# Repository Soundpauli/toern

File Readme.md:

# TŒRN `[tɜːn]`

**Open-source sequencer and sampler** — by [warft_ctrl](mailto:info@toern.live)

> Say it like *turn*. As in: turn the knobs. Turn a doodle into a beat. Turn “I can’t play piano” into “wait, that slap though.”

TŒRN is a sequenced musical device for beginners, makers, and anyone who likes blinking lights more than plugin menus. Think **Etch-A-Sketch™ energy**, but instead of drawing a wobbly staircase you draw drums, synths, and happy accidents — on a vivid **32×16 RGB LED panel** (standard; 16×16 optional) that is both the screen *and* the keyboard.

It sits on a Teensy 4.1, runs from a Micro SD card full of your WAVs, and is happy on a desk, in a backpack, or on battery at the park where strangers will ask “what *is* that?”

**Status:** under very active development. Things move fast. Stay tuned, and don’t be surprised if yesterday’s weird bug is today’s charming feature (or the other way around).

---

## What it is (in plain language)

You get:

- **8 sample voices** for drums, one-shots, loops, and “that weird recording from the metro”
- **1 three-voice polyphonic synth** with presets (bass, keys, chiptune, pads… the usual suspects)
- **2 monophonic synths** with LFO and arpeggiator for leads that refuse to sit still
- A **32-step × 8-page** sequencer (256 steps of room to overthink; 16×16 mode uses 16 steps × 16 pages), page chaining into songs, MIDI in/out, filters, bitcrush, reverb, and enough real-time knobs to keep your hands busy and your laptop jealous

No laptop required once it’s built. Samples live on the SD card. Patterns autosave. You twist, tap, and suddenly it’s 2 a.m.

For the friendly guided tour (first beat in about a minute), open the **[handbook](docs/handbook/index.html)** in this repo.

---

## A tiny history

TŒRN builds on the legacy of the **NI404**, with more features, fewer cables dangling off the side, and a custom PCB where everything mounts cleanly. The older “extra boards and hope” era is over.

Meet the glow-up:

- **RGB-I2C rotary encoders** — smoother, prettier, and they light up like they mean it
- **Custom PCB** — codec, charging, and jacks on one board
- **USB-C** — because micro-USB was a character-building experience we no longer need
- **LiPo charging port** — optional battery for true “make beats on a train” energy (battery not included; we trust you with electricity)
- **Proper audio I/O** — 6.35 mm headphone out, line in/out, mic in, *plus* a built-in mic for “sample the room right now” moments
- **TRS MIDI in/out** — play nice with the rest of your setup
- **On/off switch** — underrated luxury
- **Touch buttons** — for the things knobs shouldn’t monopolize
- **Laser-cut acrylic case** — files included; looks finished, not “breadboard cosplay”
- **JST connectors** — expansion leads plug in

Open source as always: schematics, code, and design files are here for you to poke, fork, and improve.

---

## Feature list

### Sequencer

- **11 instrument voices** on a 16-row grid: 8 sample voices (1–8), one 3-voice poly synth (11), two mono synths (13–14)
- Standard **32 steps per page × 8 pages** → 256 steps per pattern; optional 16×16 mode uses 16 steps × 16 pages
- **Voice mode**: each voice keeps its own pattern length. It loops the pages that hold its notes, pitches included, while the other voices keep looping on their own
- **FIRE** (ETC → ADV menu): optional playhead sparks when a chosen voice’s notes light white
- Store up to **999 patterns**, **999 samples**, **999 samplepacks**
- **Autosave / autoload** so your 3 a.m. genius doesn’t vanish at boot
- **Switch patterns live** without stopping playback
- **Song mode**: chain up to **64** page assignments from the current pattern
- Pattern ops: copy/paste, transpose page/channel (±1 octave), smart random notes (major/minor + rhythm ideas), clear page/channel
- **SWAP** exchanges notes between voices, with octave offsets; optional **SUBP** file subpatterns extend arrangements

### Sample voices (channels 1–8)

- Up to **~12 seconds** per voice at 44.1 kHz
- Browse and load samples **while playing** (yes, really)
- Per-voice start/end trim, forward/reverse
- **TIME** stretches or shortens samples independently of pitch
- Samplepacks (including pack 0 = custom per-voice assignment)
- Record from **built-in mic / line-in / mic-in** straight in the sample browser
- Save or merge used samples back to the SD card as a pack

### Synth voices

**Channel 11 — poly synth**

- 3 oscillators per voice × 3 voices
- Presets: BASS, KEYS, CHPT, PAD, WOW, ORG, FLT, LEAD, ARP, BRSS
- Per-voice ADSR, filter envelope, pan, volume, pitch (cents & semitones), waveform

**Channels 13–14 — mono synths**

- 2 oscillators each
- ADSR, LFO on cutoff/resonance, MIDI arpeggiator (step/span; does not pitch-shift grid notes)
- Waveforms: sine, saw, square, triangle

### Effects (all channels)

- **ADSR** — attack / decay / sustain / release (0–32 range)
- **Bitcrusher** — bit depth 1–16 (0 = bypass), sample-rate reduction down to glorious crunch
- **Filter** — LP / HP / BP, 0–10 kHz, resonance 0.7–5.0, smooth transitions
- **Reverb** — room size, damping, wet/dry; denser six-comb/four-diffuser network on reverb-equipped voices
- Fast filter access on encoder #3 during runtime (assignable default per channel)

### MIDI, clock & extras

- TRS MIDI in/out, clock send/receive, notes, transport
- BPM **40–300**, internal clock, external MIDI clock, tap tempo via touch
- Live recording / looping (touch-hold), up to ~12 s per voice
- Note probability, velocity, condition triggers (those “only every other bar” tricks)
- Global transpose, per-channel detune & octave, fine cents on the poly synth
- Mute / solo, pattern modes (OFF, ON, SONG, NEXT)
- Stereo routing options
- USB **Audio + Serial**: send the mix to a computer while using the SD tool; musical MIDI uses the TRS ports
- Analog clock **out (J25)**, clock **in (J26)** and voice-triggered **sidechain out (J27)**
- **TOUCHY** performance pads, live fills, and per-voice audition
- Browser tools for firmware flashing, SD transfers, sample conversion and the simulator
- **Demo animation:** open **ETC → INFO**, press **touch3 / BUTTON_C**; press and release **Touch 1 / BUTTON_A** to return to INFO

---

## Tech specs

| | |
|---|---|
| **Brain** | Teensy 4.1, PSRAM fitted. Audio codec is the SGTL5000 on the carrier |
| **Memory** | 16 MB PSRAM target; Micro SD (handbook suggests up to 64 GB, SanDisk Ultra) |
| **Audio** | 44.1 kHz, 16-bit mono WAV |
| **Controls** | 4× RGB illuminated I2C rotary-push encoders, 5 capacitive touch buttons |
| **Display** | Standard [32×16 RGB LED panel](https://de.aliexpress.com/item/1005010071864259.html), 512 LEDs (FastLED); 16×16 optional |
| **I/O** | 6.35 mm headphones, line in/out, mic in; built-in mic; TRS MIDI in/out |
| **Power** | USB-C or optional LiPo + charging |

---

## Repo map (where stuff lives)

| Path | Contents |
|------|----------|
| `platformio/` | Arduino sketch tabs, headers, custom audio in `src/`, build scripts and `platformio.ini` |
| `hardware/PCB/` | KiCad boards, schematics, manufacturing files and [purchasing BOMs](hardware/PCB/BOM/README.md) |
| `hardware/housing/` | Fusion archives, laser DXFs and panel previews |
| `docs/devdocs/` | Developer documentation → [docs.toern.live](https://docs.toern.live/) |
| `docs/handbook/` | Operator handbook → [handbook.toern.live](https://handbook.toern.live/) |
| `docs/BUILD.md`, `docs/info.md` | Hardware assembly and firmware build instructions |
| `tools/firmware/` | Browser firmware flasher (GPL-3.0) |
| `tools/sdtool/` | Browser SD tool |
| `tools/sim/` | Browser simulator |
| `tools/audioconvert/` | Standalone sample converter |
| `tools/case/` | Standalone case generator; `case.toern.live` planned, not deployed |
| `tools/colorsheme/`, `tools/_shared/` | Color editor and shared tool assets |
| `_debug/` | Host tests, analysis scripts and local diagnostic captures |
| `_private/` | Local business data/helpers; annotation tool in `_private/helpers/annotate/` |
| `website/` | Public project website only; local/deploy-only |

See [the complete directory map](docs/REPOSITORY_LAYOUT.md) for local-only items marked `***`.

Build from the repository root with `pio run -d platformio`, or `cd platformio` first.

For a personal hardware build, follow the [assembly and laser-cutting guide](docs/BUILD.md).
Start with the [BOM directory](hardware/PCB/BOM/README.md): check assembly-part stock
before ordering the PCB. The [pre-order list](hardware/PCB/BOM/preorder-parts.csv)
lists parts to secure for JLCPCB assembly. Then buy the
Teensy, PSRAM, encoders, matrix, cables and
case hardware separately. The website’s **Build** chapter covers the same assembly order.

---

## External libraries & modifications

This project leans on several libraries. Some are stock; some got lovingly (and necessary-ly) poked.

### Modified

- **ResamplingReader.h** (`teensy-variable-playback`)
  Variable rates, interpolation, multi-channel, loop types (repeat / ping-pong), crossfading — in `platformio/src/resamplerReader.h`

- **Treeverb** (`effect_treeverb`)
  Full-rate reverb with balanced 6/4 diffusion in RAM1 — `platformio/src/effect_treeverb.*`; the older `effect_freeverb_dmabuf` remains a host-test reference.

- **FastLED**
  `FASTLED_ALLOW_INTERRUPTS 0` so LEDs and audio don’t argue mid-beat; custom `FastLEDshow()` / `FastLEDclear()` wrappers

- **MIDI**
  Bigger Serial8 buffers for dense clock traffic (`RX 2048`, `TX 128`) and custom TRS MIDI settings

### Standard / upstream

- **TeensyPolyphony** by Nic Newdigate — polyphonic heart of the thing
- **Audio Library** (PJRC)
- **WS2812Serial**, **i2cEncoderLibV2**, **FastTouch**

---

## Get one

Order a TŒRN at **[toern.live](https://toern.live/)**. Questions go to **info@toern.live**.

When it arrives, open the **[handbook](docs/handbook/index.html)** and start at First beat. Power is USB-C. A battery and a microSD card are not in the parcel; the buy page and the handbook hardware chapter name what to get.

Firmware changes: [`info.md`](docs/info.md) to flash, [`docs/devdocs/`](docs/devdocs) for how the code is shaped, [`firmware-edits`](docs/devdocs/docs/contributing/firmware-edits.md) for a new menu page. Fabricating a board from the design files is [`BUILD.md`](docs/BUILD.md) — that is not how a TŒRN is ordered.

---

## License

- **Software / code**: [MIT](LICENSE) — free for personal and commercial use.
- **Firmware loader** (`tools/firmware/`): [GPL-3.0](tools/firmware/LICENSE), because that tool is Teensy Loader Javascript. GPL-3.0 applies only to that folder.
- **Hardware design files** (schematics, PCB layouts, Gerbers, housings, etc.): [CC BY-NC 4.0](https://creativecommons.org/licenses/by-nc/4.0/) — personal / non-commercial use and modification. **Jan-Peter Kuntoff is the only person authorized to sell TŒRN hardware** (bare PCB, assembled PCB, kit, or unit), including boards sold **without a Teensy**. Teensy 4.1 is PJRC’s; it is not licensed in this repo. Anyone else needs written consent to sell.

Commercial hardware licensing: Jan aka **warft_ctrl** — info@toern.live (Hamburg, Germany)

---

## Thank you

Huge thanks to **Paul Stoffregen** and the PJRC crew for Teensy, to the wider open-source audio community, and an especially loud shoutout to **Nic Newdigate** for teensy-polyphony — basically the soul of this project.

Made with too many late nights and exactly the right number of RGB LEDs.

**Jan aka warft_ctrl** (formerly soundpauli)
Hamburg, 2026

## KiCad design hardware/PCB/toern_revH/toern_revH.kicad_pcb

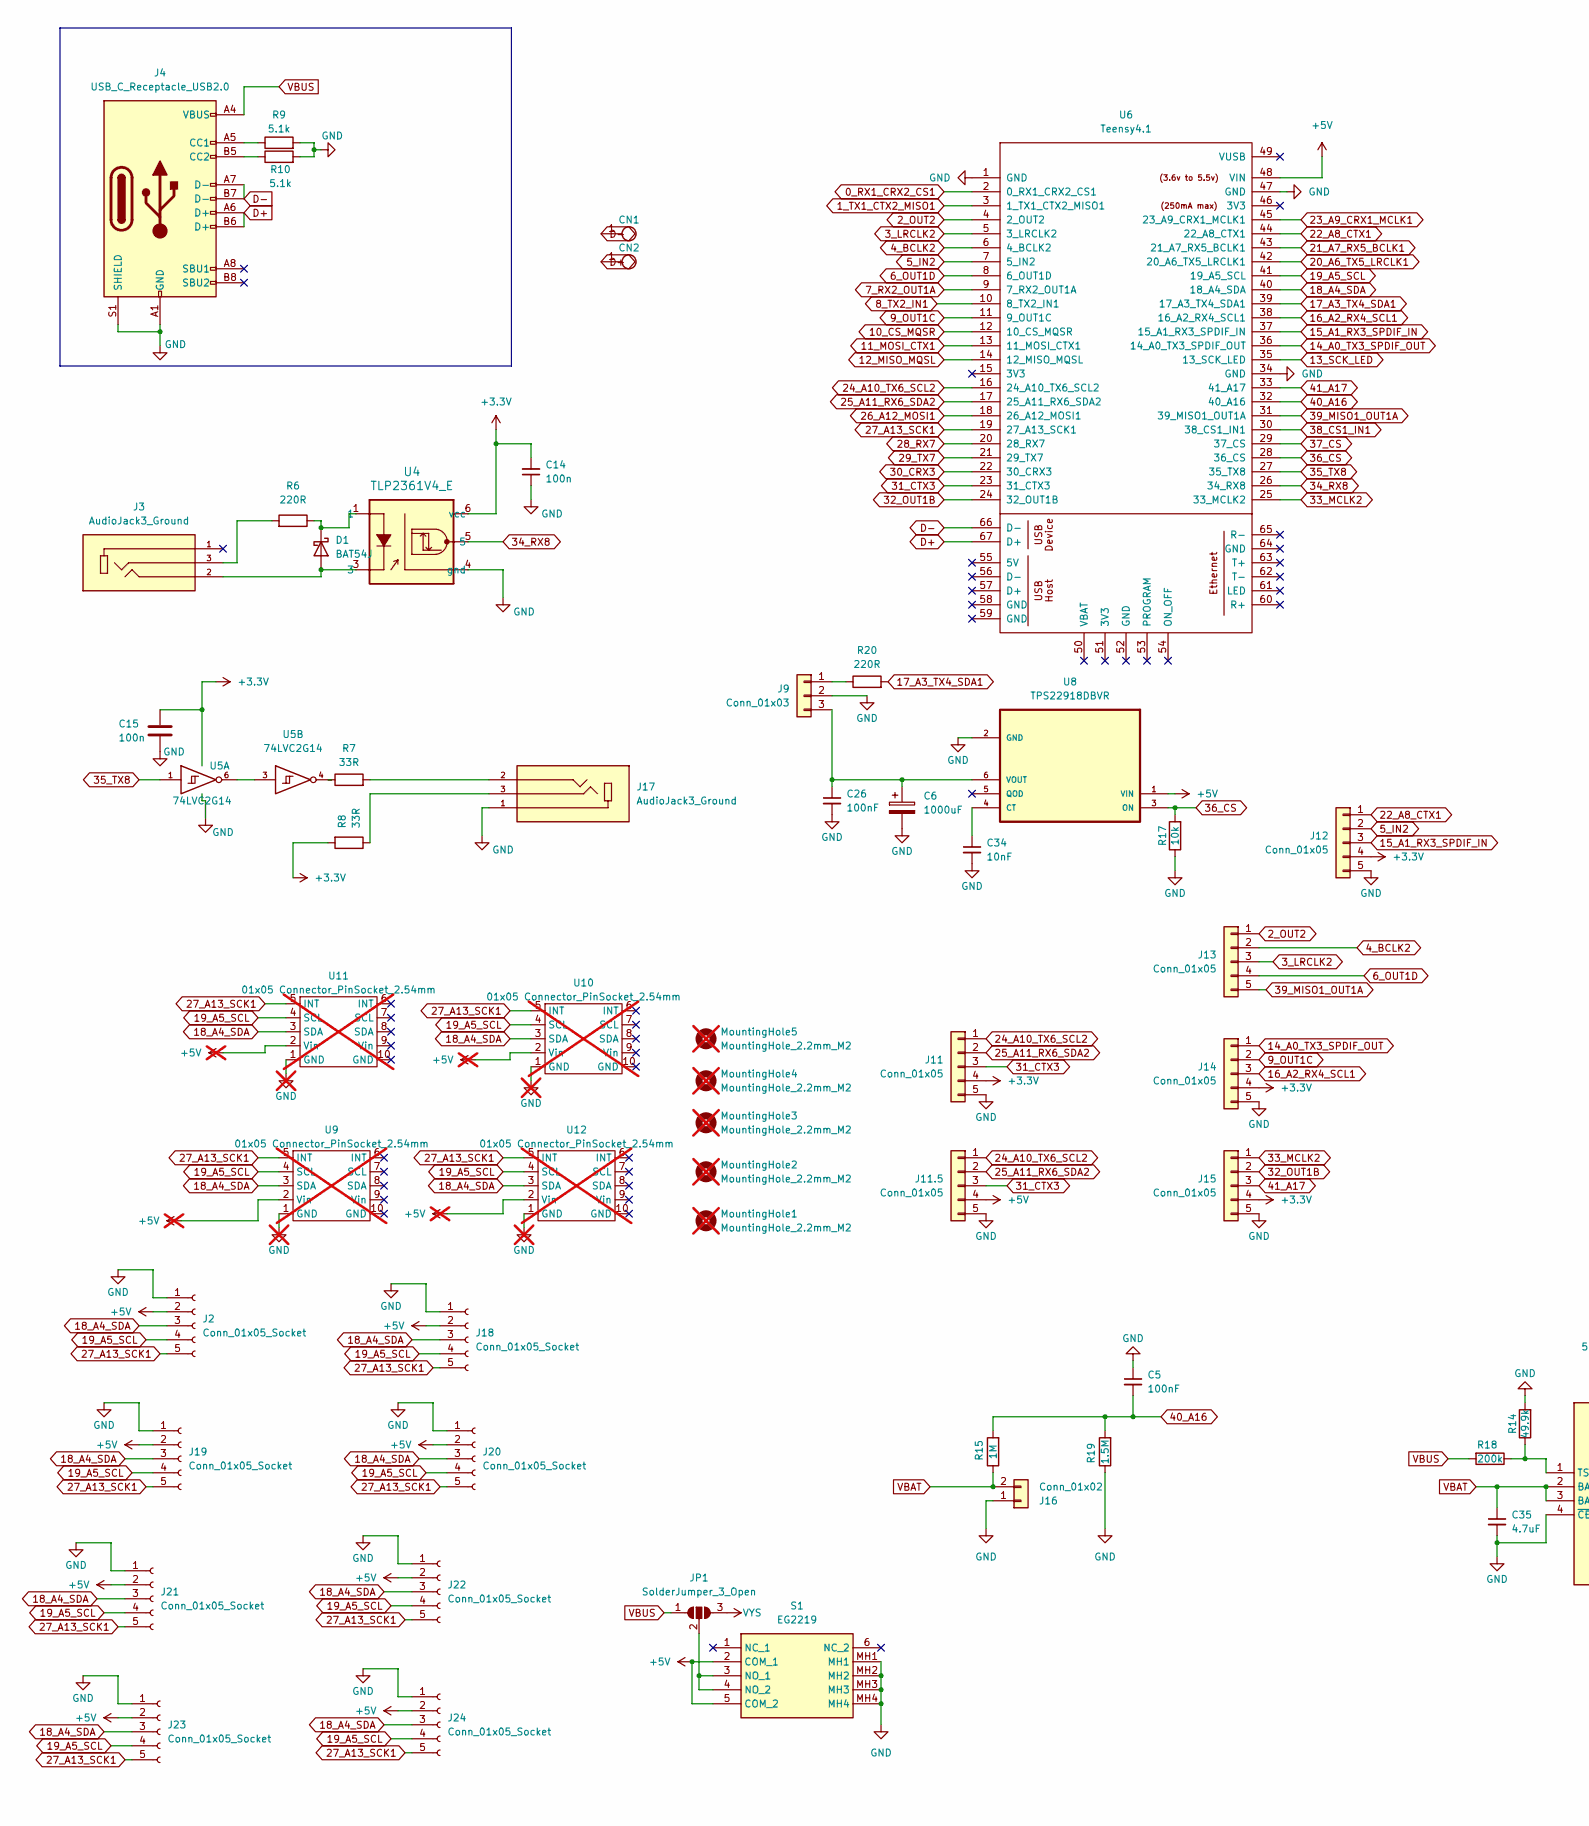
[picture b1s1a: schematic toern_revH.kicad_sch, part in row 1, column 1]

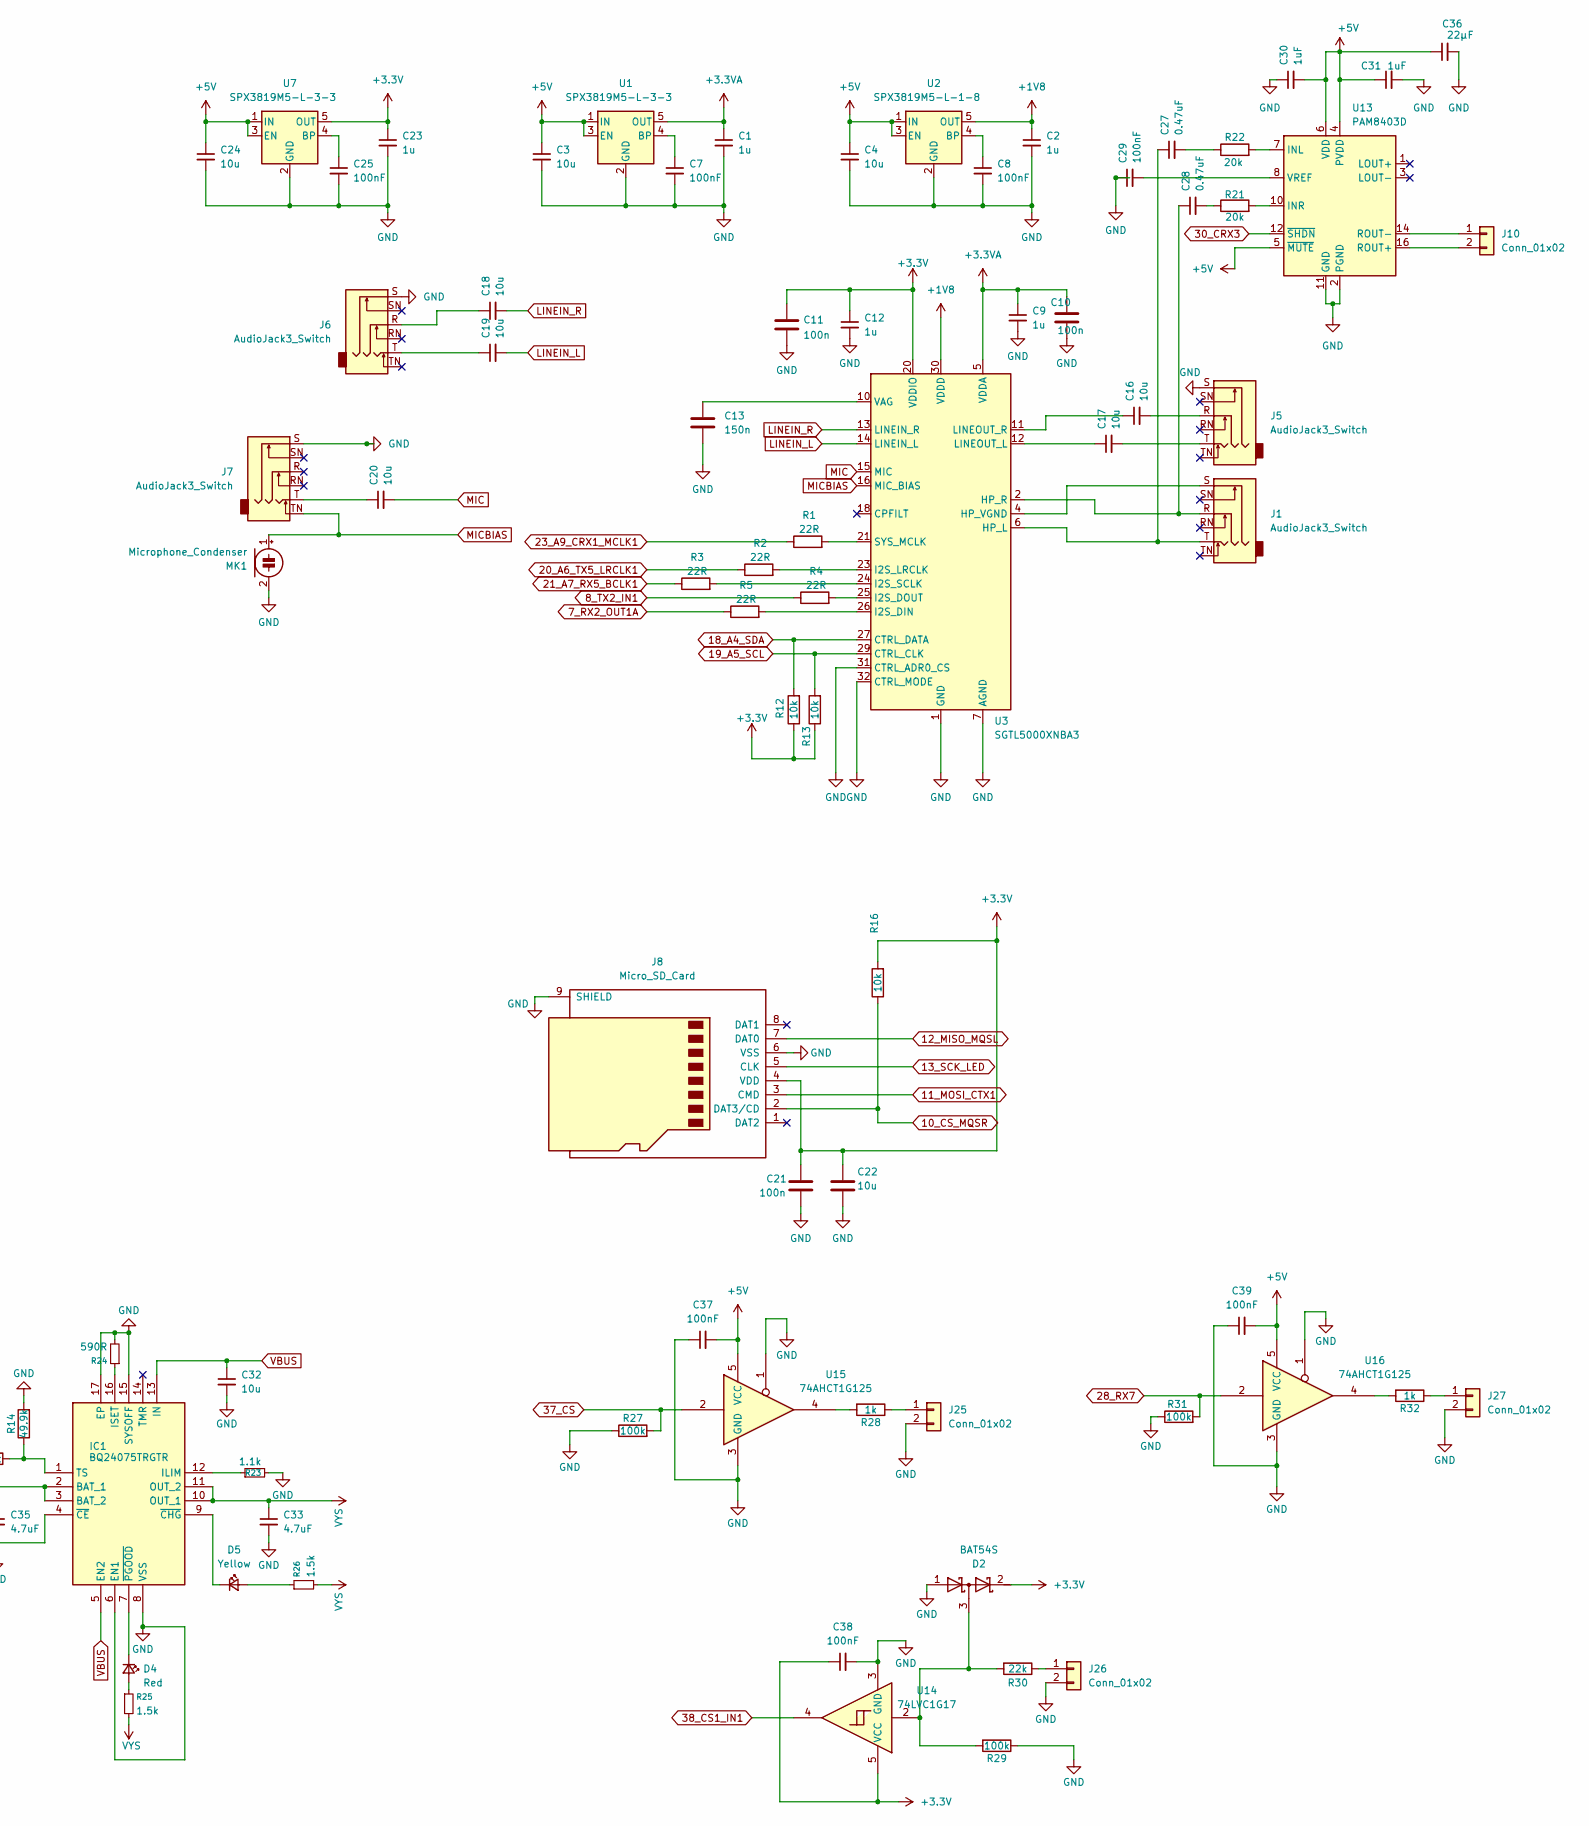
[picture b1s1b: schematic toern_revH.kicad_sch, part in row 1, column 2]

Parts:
C1, C2, C9, C12, C23: 1u; C_0402_1005Metric; lcsc# C52923
C3, C4, C16, C17, C18, C19, C20, C22, C24, C32: 10u; C_0603_1608Metric; lcsc# C19702
C5, C26, C29: 100nF; C_0603_1608Metric; lcsc# C1590
C6: 1000uF; CP_Elec_8x10.5; lcsc# C5686929
C7, C8, C25, C37, C38, C39: 100nF; C_0402_1005Metric; lcsc# C1525
C10, C11: 100n; C_0402_1005Metric; MPN CC0603KRX7R6BB224; lcsc# C77020
C13: 150n; C_0402_1005Metric; lcsc# C162182
C14, C15, C21: 100n; C_0402_1005Metric; lcsc# C77020
C27, C28: 0.47uF; C_0603_1608Metric; lcsc# C1623
C30, C31: 1uF; C_0603_1608Metric; lcsc# C15849
C33, C35: 4.7uF; C_0603_1608Metric; lcsc# C1705
C34: 10nF; C_0402_1005Metric; lcsc# C15195
C36: 22µF; C_0603_1608Metric; lcsc# C59461
CN1, CN2: YZP0354-20100-01; MPN YZP0354-20100-01; lcsc# C5157282
D1: BAT54J; D_SOD-323F; lcsc# C130415
D2: BAT54S; SOT-23; lcsc# C171786
D4: Red; LED_0402_1005Metric; lcsc# C71911
D5: Yellow; LED_0402_1005Metric; lcsc# C74342
IC1: BQ24075TRGTR; QFN50P300X300X100-17N-D; Mouser Part Number 595-BQ24075TRGTR
J1, J5, J6, J7: AudioJack3_Switch; Jack_6.35mm_Neutrik_NMJ6HCD2_Horizontal; lcsc# C368502
J2, J18, J19, J20, J21, J22, J23, J24: Conn_01x05_Socket; PinSocket_1x05_P2.54mm_Vertical; lcsc# C50950
J3, J17: AudioJack3_Ground; CUI_SJ1-3533; PARTREV 1.01; lcsc# C4991776
J4: USB_C_Receptacle_USB2.0; USB_C_Receptacle_HRO_TYPE-C-31-M-12; lcsc# C165948
J8: Micro_SD_Card; microSD_HC_Hirose_DM3BT-DSF-PEJS; lcsc# C597972
J9: Conn_01x03; JST_PH_B3B-PH-K_1x03_P2.00mm_Vertical; lcsc# C131339
J10, J16, J25, J26, J27: Conn_01x02; JST_PH_B2B-PH-K_1x02_P2.00mm_Vertical; lcsc# C131337
J11, J11.5, J12, J13, J14, J15: Conn_01x05; JST_PH_B5B-PH-K_1x05_P2.00mm_Vertical; lcsc# C157993
JP1: SolderJumper_3_Open; SolderJumper-3_P1.3mm_Open_RoundedPad1.0x1.5mm
MK1: Microphone_Condenser; MIC-TH_BD6.0-P1.90-D0.4-L-FD; lcsc# C529951
MountingHole1, MountingHole2, MountingHole3, MountingHole4, MountingHole5: MountingHole_2.2mm_M2; not fitted
R1, R2, R3, R4, R5: 22R; R_0402_1005Metric; lcsc# C25092
R6, R20: 220R; R_0603_1608Metric; lcsc# C22962
R7, R8: 33R; R_0603_1608Metric; lcsc# C23140
R9, R10: 5.1k; R_0402_1005Metric; lcsc# C25905
R12, R13, R16, R17: 10k; R_0402_1005Metric; lcsc# C25744
R14: 49.9k; R_0402_1005Metric; lcsc# C100457
R15: 1M; R_0402_1005Metric; lcsc# C26083
R18: 200k; R_0402_1005Metric; lcsc# C25764
R19: 1.5M; R_0402_1005Metric; lcsc# C11812
R21, R22: 20k; R_0805_2012Metric; LCSC C4328
R23: 1.1k; R_0402_1005Metric; lcsc# C25860
R24: 590R; R_0402_1005Metric; lcsc# C166635
R25, R26: 1.5k; R_0402_1005Metric; lcsc# C25867
R27, R29, R31: 100k; R_0402_1005Metric; lcsc# C25741
R28, R32: 1k; R_0402_1005Metric; lcsc# C11702
R30: 22k; R_0402_1005Metric; lcsc# C25768
S1: EG2219; Mouser Part Number 612-EG2219
U1, U7: SPX3819M5-L-3-3; SOT-23-5; lcsc# C9055
U2: SPX3819M5-L-1-8; SOT-23-5; lcsc# C24639
U3: SGTL5000XNBA3; QFN-32-1EP_5x5mm_P0.5mm_EP3.6x3.6mm; lcsc# C5196742
U4: TLP2361V4_E; 5pin SO6_TOS; lcsc# C107626
U5: 74LVC2G14; SOT-23-6; LCSC Part # C12401
U6: Teensy4.1; Teensy41; lcsc# ----
U8: TPS22918DBVR; SOT95P280X145-6N; lcsc# C131941
U9, U10, U11, U12: 01x05 Connector_PinSocket_2.54mm; DuppaI2CEncoderV2.1; lcsc# C50950; not fitted
U13: PAM8403D; SOIC-16_3.9x9.9mm_P1.27mm; lcsc# C17337
U14: 74LVC1G17; SOT-23-5; lcsc# C7836
U15, U16: 74AHCT1G125; SOT-23-5; lcsc# C7484

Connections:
0_RX1_CRX2_CS1: U6.2 (0_RX1_CRX2_CS1)
1_TX1_CTX2_MISO1: U6.3 (1_TX1_CTX2_MISO1)
2_OUT2: J13.1, U6.4 (2_OUT2); also elsewhere on the board
3_LRCLK2: J13.3, U6.5 (3_LRCLK2); also elsewhere on the board
4_BCLK2: J13.2, U6.6 (4_BCLK2); also elsewhere on the board
5_IN2: J12.2, U6.7 (5_IN2); also elsewhere on the board
6_OUT1D: J13.4, U6.8 (6_OUT1D); also elsewhere on the board
7_RX2_OUT1A: R5.1, U6.9 (7_RX2_OUT1A)
8_TX2_IN1: R4.1, U6.10 (8_TX2_IN1)
9_OUT1C: J14.2, U6.11 (9_OUT1C); also elsewhere on the board
10_CS_MQSR: J8.2 (DAT3/CD), R16.1, U6.12 (10_CS_MQSR)
11_MOSI_CTX1: J8.3 (CMD), U6.13 (11_MOSI_CTX1)
12_MISO_MQSL: J8.7 (DAT0), U6.14 (12_MISO_MQSL)
13_SCK_LED: J8.5 (CLK), U6.35 (13_SCK_LED)
14_A0_TX3_SPDIF_OUT: J14.1, U6.36 (14_A0_TX3_SPDIF_OUT); also elsewhere on the board
15_A1_RX3_SPDIF_IN: J12.3, U6.37 (15_A1_RX3_SPDIF_IN); also elsewhere on the board
16_A2_RX4_SCL1: J14.3, U6.38 (16_A2_RX4_SCL1); also elsewhere on the board
17_A3_TX4_SDA1: R20.2, U6.39 (17_A3_TX4_SDA1)
18_A4_SDA: J2.3, J18.3, J19.3, J20.3, J21.3, J22.3, J23.3, J24.3, R12.2, U3.27 (CTRL_DATA), U6.40 (18_A4_SDA), U9.3 (SDA), U10.3 (SDA), U11.3 (SDA), U12.3 (SDA)
19_A5_SCL: J2.4, J18.4, J19.4, J20.4, J21.4, J22.4, J23.4, J24.4, R13.2, U3.29 (CTRL_CLK), U6.41 (19_A5_SCL), U9.4 (SCL), U10.4 (SCL), U11.4 (SCL), U12.4 (SCL)
20_A6_TX5_LRCLK1: R2.1, U6.42 (20_A6_TX5_LRCLK1)
21_A7_RX5_BCLK1: R3.1, U6.43 (21_A7_RX5_BCLK1)
22_A8_CTX1: J12.1, U6.44 (22_A8_CTX1); also elsewhere on the board
23_A9_CRX1_MCLK1: R1.1, U6.45 (23_A9_CRX1_MCLK1)
24_A10_TX6_SCL2: J11.1, J11.5.1, U6.16 (24_A10_TX6_SCL2); also elsewhere on the board
25_A11_RX6_SDA2: J11.2, J11.5.2, U6.17 (25_A11_RX6_SDA2); also elsewhere on the board
26_A12_MOSI1: U6.18 (26_A12_MOSI1)
27_A13_SCK1: J2.5, J18.5, J19.5, J20.5, J21.5, J22.5, J23.5, J24.5, U6.19 (27_A13_SCK1), U9.5 (INT), U10.5 (INT), U11.5 (INT), U12.5 (INT)
28_RX7: R31.2, U6.20 (28_RX7), U16.2
29_TX7: U6.21 (29_TX7)
30_CRX3: U6.22 (30_CRX3), U13.12 (~SHDN)
31_CTX3: J11.3, J11.5.3, U6.23 (31_CTX3); also elsewhere on the board
32_OUT1B: J15.2, U6.24 (32_OUT1B)
33_MCLK2: J15.1, U6.25 (33_MCLK2)
34_RX8: U4.5, U6.26 (34_RX8)
35_TX8: U5.1, U6.27 (35_TX8)
36_CS: R17.2, U6.28 (36_CS), U8.3 (ON)
37_CS: R27.2, U6.29 (37_CS), U15.2
38_CS1_IN1: U6.30 (38_CS1_IN1), U14.4
39_MISO1_OUT1A: J13.5, U6.31 (39_MISO1_OUT1A); also elsewhere on the board
40_A16: C5.2, R15.2, R19.2, U6.32 (40_A16)
41_A17: J15.3, U6.33 (41_A17)
+1V8: C2.1, U2.5 (OUT), U3.30 (VDDD)
+3.3V: C11.1, C12.1, C14.2, C15.1, C21.2, C22.1, C23.1, C38.1, D2.2 (K), J8.4 (VDD), J11.4, J12.4, J14.4, J15.4, R8.2, R12.1, R13.1, R16.2, U3.20 (VDDIO), U4.6 (vcc), U5.5 (VCC), U7.5 (OUT), U14.5 (VCC); also elsewhere on the board
+3.3VA: C1.1, C9.1, C10.1, U1.5 (OUT), U3.5 (VDDA)
+5V: C3.1, C4.1, C24.1, C30.2, C31.1, C36.1, C37.2, C39.2, J2.2, J11.5.4, J18.2, J19.2, J20.2, J21.2, J22.2, J23.2, J24.2, S1.2 (COM_1), S1.5 (COM_2), U1.1 (IN), U1.3 (EN), U2.1 (IN), U2.3 (EN), U6.48 (VIN), U7.1 (IN), U7.3 (EN), U8.1 (VIN), U9.2 (Vin), U10.2 (Vin), U11.2 (Vin), U12.2 (Vin), U13.4 (PVDD), U13.5 (~MUTE), U13.6 (VDD), U13.13 (PVDD), U15.5 (VCC), U16.5 (VCC); also elsewhere on the board
D+: CN2.1 (CONTACT), J4.A6 (D+), J4.B6 (D+), U6.67 (D+)
D-: CN1.1 (CONTACT), J4.A7 (D-), J4.B7 (D-), U6.66 (D-)
GND: C1.2, C2.2, C3.2, C4.2, C5.1, C6.2, C7.2, C8.2, C9.2, C10.2, C11.2, C12.2, C13.2, C14.1, C15.2, C21.1, C22.2, C23.2, C24.2, C25.2, C26.2, C29.1, C30.1, C31.2, C32.2, C33.2, C34.2, C35.2, C36.2, C37.1, C38.2, C39.1, D2.1 (A), IC1.4 (~CE), IC1.6 (EN1), IC1.8 (VSS), IC1.15 (SYSOFF), IC1.17 (EP), J2.1, J4.A1 (GND), J4.A12 (GND), J4.B1 (GND), J4.B12 (GND), J4.S1 (SHIELD), J5.S, J6.S, J7.S, J8.6 (VSS), J8.9 (SHIELD), J9.2, J11.5, J11.5.5, J12.5, J14.5, J15.5, J16.1, J17.1, J18.1, J19.1, J20.1, J21.1, J22.1, J23.1, J24.1, J25.2, J26.2, J27.2, MK1.2 (-), R9.2, R10.2, R14.2, R17.1, R19.1, R23.2, R24.2, R27.1, R29.1, R31.1, S1.MH1, S1.MH2, S1.MH3, S1.MH4, U1.2 (GND), U2.2 (GND), U3.1 (GND), U3.3 (GND), U3.7 (AGND), U3.31 (CTRL_ADR0_CS), U3.32 (CTRL_MODE), U3.33 (GND), U4.4 (gnd), U5.2 (GND), U6.1 (GND), U6.34 (GND), U6.47 (GND), U7.2 (GND), U8.2 (GND), U9.1 (GND), U10.1 (GND), U11.1 (GND), U12.1 (GND), U13.2 (PGND), U13.11 (GND), U13.15 (PGND), U14.3 (GND), U15.1, U15.3 (GND), U16.1, U16.3 (GND); also elsewhere on the board
LINEIN_L: C19.2, U3.14 (LINEIN_L)
LINEIN_R: C18.2, U3.13 (LINEIN_R)
MIC: C20.2, U3.15 (MIC)
MICBIAS: J7.TN, MK1.1 (+), U3.16 (MIC_BIAS)
unnamed: C16.2, J5.R
unnamed: C17.2, J5.T
unnamed: C18.1, J6.R
unnamed: C19.1, J6.T
unnamed: C20.1, J7.T
unnamed: C27.2, R22.1
unnamed: C28.2, R21.1
unnamed: D1.2 (A), J3.2, U4.3
unnamed: D1.1 (K), R6.1, U4.1
unnamed: D2.3 (common), R29.2, R30.2, U14.2
unnamed: D4.2 (A), R25.1
unnamed: D4.1 (K), IC1.7 (~PGOOD)
unnamed: D5.2 (A), R26.1
unnamed: D5.1 (K), IC1.9 (~CHG)
unnamed: IC1.12 (ILIM), R23.1
unnamed: IC1.16 (ISET), R24.1
unnamed: IC1.1 (TS), R14.1, R18.1
unnamed: J3.3, R6.2
unnamed: J4.A5 (CC1), R9.1
unnamed: J4.B5 (CC2), R10.1
unnamed: J9.1, R20.1
unnamed: C6.1, C26.1, J9.3, U8.6 (VOUT)
unnamed: J10.1, U13.14 (ROUT-)
unnamed: J10.2, U13.16 (ROUT+)
unnamed: J17.2, R7.2
unnamed: J17.3, R8.1
unnamed: J25.1, R28.1
unnamed: J26.1, R30.1
unnamed: J27.1, R32.1
unnamed: JP1.2 (C), S1.3 (NO_1), S1.4 (NO_2)
unnamed: R7.1, U5.4
unnamed: R28.2, U15.4
unnamed: R32.2, U16.4
unnamed: C7.1, U1.4 (BP)
unnamed: C8.1, U2.4 (BP)
unnamed: C27.1, J1.T, U3.6 (HP_L)
unnamed: C28.1, J1.R, U3.2 (HP_R)
unnamed: J1.S, U3.4 (HP_VGND)
unnamed: R5.2, U3.26 (I2S_DIN)
unnamed: R4.2, U3.25 (I2S_DOUT)
unnamed: R2.2, U3.23 (I2S_LRCLK)
unnamed: R3.2, U3.24 (I2S_SCLK)
unnamed: C17.1, U3.12 (LINEOUT_L)
unnamed: C16.1, U3.11 (LINEOUT_R)
unnamed: R1.2, U3.21 (SYS_MCLK)
unnamed: C13.1, U3.10 (VAG)
unnamed: U5.3, U5.6
unnamed: C25.1, U7.4 (BP)
unnamed: C34.1, U8.4 (CT)
unnamed: R22.2, U13.7 (INL)
unnamed: R21.2, U13.10 (INR)
unnamed: C29.2, U13.8 (VREF)
VBAT: C35.1, IC1.2 (BAT_1), IC1.3 (BAT_2), J16.2, R15.1
VBUS: C32.1, IC1.5 (EN2), IC1.13 (IN), J4.A4 (VBUS), J4.A9 (VBUS), J4.B4 (VBUS), J4.B9 (VBUS), JP1.1 (A), R18.2
VYS: C33.1, IC1.10 (OUT_1), IC1.11 (OUT_2), JP1.3 (B), R25.2, R26.2

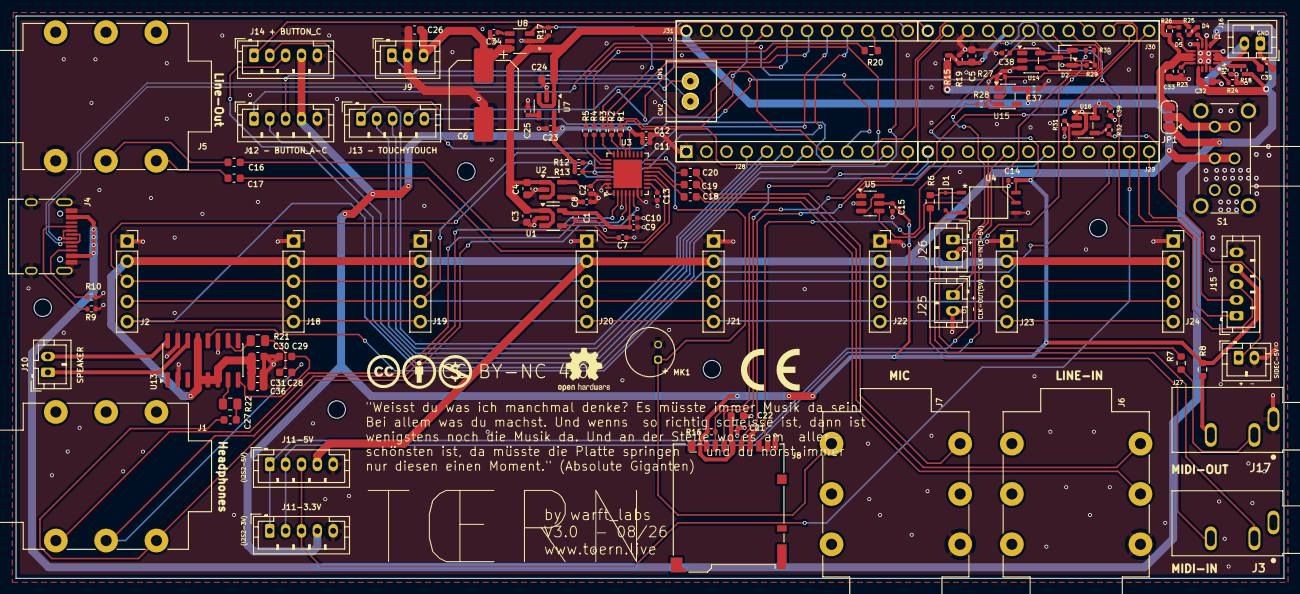
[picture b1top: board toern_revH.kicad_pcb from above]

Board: 4 copper layers, 160.0 x 71.0 mm, 130 parts (0 on the bottom side), 104 nets.

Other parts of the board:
J11-3.3V, J11-5V, J12 - BUTTON_A-C, J13 - TOUCHYTOUCH, J14 + BUTTON_C: Conn_01x05; JST_PH_B5B-PH-K_1x05_P2.00mm_Vertical
J28, J29, J30, J31: 929870-01-12-RA; 3M_929870-01-12-RA_Assembly
LOGOOPENHARDWARE: OSHW-Logo2_7.3x6mm_SilkScreen

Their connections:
2_OUT2: J13 - TOUCHYTOUCH.1; also elsewhere on the board
3_LRCLK2: J13 - TOUCHYTOUCH.3; also elsewhere on the board
4_BCLK2: J13 - TOUCHYTOUCH.2; also elsewhere on the board
5_IN2: J12 - BUTTON_A-C.2; also elsewhere on the board
6_OUT1D: J13 - TOUCHYTOUCH.4; also elsewhere on the board
9_OUT1C: J14 + BUTTON_C.2; also elsewhere on the board
14_A0_TX3_SPDIF_OUT: J14 + BUTTON_C.1; also elsewhere on the board
15_A1_RX3_SPDIF_IN: J12 - BUTTON_A-C.3; also elsewhere on the board
16_A2_RX4_SCL1: J14 + BUTTON_C.3; also elsewhere on the board
22_A8_CTX1: J12 - BUTTON_A-C.1; also elsewhere on the board
24_A10_TX6_SCL2: J11-3.3V.1, J11-5V.1; also elsewhere on the board
25_A11_RX6_SDA2: J11-3.3V.2, J11-5V.2; also elsewhere on the board
31_CTX3: J11-3.3V.3, J11-5V.3; also elsewhere on the board
39_MISO1_OUT1A: J13 - TOUCHYTOUCH.5; also elsewhere on the board
+3.3V: J11-3.3V.4, J12 - BUTTON_A-C.4, J14 + BUTTON_C.4; also elsewhere on the board
+5V: J11-5V.4; also elsewhere on the board
GND: J11-3.3V.5, J11-5V.5, J12 - BUTTON_A-C.5, J14 + BUTTON_C.5; also elsewhere on the board

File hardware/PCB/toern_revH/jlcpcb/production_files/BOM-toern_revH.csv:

Comment,Designator,Footprint,LCSC,Quantity
0.47uF,"C27,C28",C_0603_1608Metric,C1623,2
1.1k,R23,R_0402_1005Metric,C25860,1
1.5M,R19,R_0402_1005Metric,C11812,1
1.5k,"R25,R26",R_0402_1005Metric,C25867,2
1000uF,C6,CP_Elec_8x10.5,C5686929,1
100k,"R27,R29,R31",R_0402_1005Metric,C25741,3
100n,"C10,C11,C14,C15,C21",C_0402_1005Metric,C77020,5
100nF,"C25,C37,C38,C39,C7,C8",C_0402_1005Metric,C1525,6
100nF,"C26,C29,C5",C_0603_1608Metric,C1590,3
10k,"R12,R13,R16,R17",R_0402_1005Metric,C25744,4
10nF,C34,C_0402_1005Metric,C15195,1
10u,"C16,C17,C18,C19,C20,C22,C24,C3,C32,C4",C_0603_1608Metric,C19702,10
150n,C13,C_0402_1005Metric,C162182,1
1M,R15,R_0402_1005Metric,C26083,1
1k,"R28,R32",R_0402_1005Metric,C11702,2
1u,"C1,C12,C2,C23,C9",C_0402_1005Metric,C52923,5
1uF,"C30,C31",C_0603_1608Metric,C15849,2
200k,R18,R_0402_1005Metric,C25764,1
20k,"R21,R22",R_0805_2012Metric,C4328,2
220R,"R20,R6",R_0603_1608Metric,C22962,2
22R,"R1,R2,R3,R4,R5",R_0402_1005Metric,C25092,5
22k,R30,R_0402_1005Metric,C25768,1
22µF,C36,C_0603_1608Metric,C59461,1
33R,"R7,R8",R_0603_1608Metric,C23140,2
4.7uF,"C33,C35",C_0603_1608Metric,C1705,2
49.9k,R14,R_0402_1005Metric,C100457,1
5.1k,"R10,R9",R_0402_1005Metric,C25905,2
590R,R24,R_0402_1005Metric,C166635,1
74AHCT1G125,"U15,U16",SOT-23-5,C7484,2
74LVC1G17,U14,SOT-23-5,C7836,1
74LVC2G14,U5,SOT-23-6,C12401,1
AudioJack3_Ground,"J17,J3",CUI_SJ1-3533,C4991776,2
AudioJack3_Switch,"J1,J5,J6,J7",Jack_6.35mm_Neutrik_NMJ6HCD2_Horizontal,C368502,4
BAT54J,D1,D_SOD-323F,C130415,1
BAT54S,D2,SOT-23,C171786,1
BQ24075TRGTR,IC1,QFN50P300X300X100-17N-D,C544783,1
Conn_01x02,"J10,J16,J25,J26,J27",JST_PH_B2B-PH-K_1x02_P2.00mm_Vertical,C131337,5
Conn_01x03,J9,JST_PH_B3B-PH-K_1x03_P2.00mm_Vertical,C131339,1
Conn_01x05,"J32,J11,J12,J13,J14,J15",JST_PH_B5B-PH-K_1x05_P2.00mm_Vertical,C157993,6
Conn_01x05_Socket,"J18,J19,J2,J20,J21,J22,J23,J24",PinSocket_1x05_P2.54mm_Vertical,C50950,8
EG2219,S1,EG2219,C3664594,1
Micro_SD_Card,J8,microSD_HC_Hirose_DM3BT-DSF-PEJS,C597972,1
Microphone_Condenser,MK1,MIC-TH_BD6.0-P1.90-D0.4-L-FD,C529951,1
PAM8403D,U13,SOIC-16_3.9x9.9mm_P1.27mm,C17337,1
Red,D4,LED_0402_1005Metric,C71911,1
SGTL5000XNBA3,U3,QFN-32-1EP_5x5mm_P0.5mm_EP3.6x3.6mm,C5196742,1
SPX3819M5-L-1-8,U2,SOT-23-5,C24639,1
SPX3819M5-L-3-3,"U1,U7",SOT-23-5,C9055,2
TLP2361V4_E,U4,5pin SO6_TOS,C107626,1
TPS22918DBVR,U8,SOT95P280X145-6N,C131941,1
USB_C_Receptacle_USB2.0,J4,USB_C_Receptacle_HRO_TYPE-C-31-M-12,C165948,1
YZP0354-20100-01,"CN1,CN2",YZP0354-20100-01,C5157282,2
Yellow,D5,LED_0402_1005Metric,C74342,1

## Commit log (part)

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2025-01-27 added MIDI-IN
2025-02-03 starting adsr implementation + bugfixing
2025-02-04 bugfixes for playback and filebrowser
2025-02-07 cleaning up files
2025-02-13 fixed bug with posString
2025-02-17 fixed sample-splicing
2025-02-26 added UI for filters
2025-02-28 splitted main files to clean
2025-03-19 added filters for V13
2025-03-19 completed synth integration 11-14
2025-03-24 added drums for ch1-3
2025-03-25 fixed filters and bugfixes plus menu
2025-03-28 Update LICENSE
    Changed HW license to CC by nc
2025-03-28 fixed sample loading and editing
2025-03-29 fixed midi In Clock
2025-03-29 fixed midi in and out
2025-03-30 fixed midi
2025-04-04 added multi osc and drums for ch1-4
2025-04-06 fixed memory issues
2025-04-08 fixed ram problems
2025-04-11 further fixed for filters and voices
2025-04-16 more fixes for synths and freqs
2025-04-24 more bugfixes and features
2025-04-26 fixed sample cutting
2025-04-29 fixed sampler and midi + ui
2025-05-07 additional bugfixes
2025-05-11 bugfixes and delay timings
2025-05-20 added touch and realtime recording
2025-05-23 fixed BPM calculations for midi
2025-05-23 fixed midi transport
2025-05-24 fixed settings and menu
2025-05-26 added fast-recording via 3.5mm pedal
2025-06-17 fixed playback and midi
2025-06-17 fixed wav selection
2025-06-18 added PMOD patternmode
2025-07-07 flattend audio setup, fixed bugs with memory during play
2025-07-15 new filter views
2025-08-21 bugfixes
2025-09-11 further bugfixes
2025-09-13 added AI
2025-09-18 bugfixes and added filters
2025-09-19 bugfixes for encoderlights and midi
2025-09-26 added subpattern mode
2025-10-04 more bugfixes and some features
2025-10-18 fixing samplepack saving
2025-10-18 fixing sampl search and midi mode
2025-10-18 added reverse samples
2025-10-18 added bugfixes for ai
2025-10-21 cleanup and new menu, songmode
2025-10-21 cleanup and new menu, songmode2
2025-10-22 added probabilies
2025-10-22 added probabilies fix
2025-10-22 added fix for multiple panels
2025-10-23 adding fixes for eepromcrash
2025-10-25 fixed reset and memory
2025-10-28 back to working version after memory/pong fail
2025-11-07 fixed recording
2025-11-08 memory opt and bugfixes
2025-11-08 memory opt and bugfixes2
2025-11-09 added PONG
2025-11-09 PONG fixes
2025-11-11 added CTRL mode play/vol
2025-11-15 fixed midi sync
2025-11-15 fixed midi sync and transport
2025-11-19 matze hat geregelt - midi läuft
2025-11-20 looper recording fixed
2025-11-25 fixed midi finally
2025-11-25 fixed midi finally + autosave fix
2025-11-26 added condition triggers
2025-11-26 added condition triggers - advanced
2025-11-26 fixed fastfilters
2025-11-26 fixed button debounce 30ms ghostplaypause
2025-11-27 fixed button debounce 30ms ghostplaypause 2
2025-11-27 changes in monitoring-in
2025-11-27 changes in monitoring-in 2
2025-11-28 changes for bpm, rec and helpers
2025-11-30 fixed memory issues with large samples
2025-12-01 fixed overflows on long runs
2025-12-06 fixes for ram1, freeverbs and more
2025-12-06 fixes for ch11 fastfilter
2025-12-06 fixes for midi channels and loudness
2025-12-06 fixed synth voices, removed DRUMS
2025-12-06 added LFO and ARPEGGIATOR ch13+14
2025-12-14 performance fix and filenames
2025-12-14 syth filter and defaults deeper
2025-12-15 UX bugfixes
2025-12-15 auto generation for NEW
2025-12-18 added alternatie draw method
2025-12-22 further fixes for menu
2025-12-27 fixed samplebrowsing for large files
2025-12-27 fixed samplerates
2025-12-27 added Channel splitting 1-4,5-8
2025-12-27 fix for ch11 bounds
2025-12-28 added error logging to sd2
2026-01-07 added play on touch
2026-01-07 fixed menu
2026-01-07 various bugfixes
2026-01-09 fixes in soundquality
2026-01-23 varoious fixes in stability
2026-01-23 reverted some fixes again
2026-01-23 fixed timer display flickering
2026-01-26 custom color shemes
2026-01-26 fixed sample preview and loader
2026-01-26 fixed sample preview and loader2
2026-02-20 various fixes
2026-02-20 clean up
2026-02-20 updated readme and info
2026-02-20 clean up kiCad Files
2026-02-20 pcb: locking unmovable parts
2026-02-20 pcb: fixing thermal relief
2026-03-02 more fixes
2026-03-09 fixes for HD Displays 32x16
2026-03-12 extended reverb and muteAll fix for Draw==R
2026-03-12 fixed PCB and shematics for RevG
2026-03-12 fixed PCB and shematics for RevG 2
2026-03-13 fixed brightnesssettings on load and save
2026-03-13 fixed menu exitpaths
2026-03-13 fixed menu and filter touch crashes
2026-03-13 fixed folder display
2026-03-17 fix drawmode==r
2026-03-17 pre-menu commit
2026-03-17 fix for sampledirection and mutes
2026-03-17 change of menu encoders
2026-03-17 better midi-in sync workflow
2026-03-17 fix for midi sync external transport
2026-03-18 fix serialColorRead()
2026-03-19 miditransport delay menu
2026-03-19 pre-memory test
2026-03-20 fixed instruments
2026-03-21 pre browser
2026-03-22 new filebrowser
2026-03-22 fixed ch13+14 noteoff
2026-03-23 check midi
2026-03-23 fixed midi ch13+14 release
2026-03-23 fixed ch13+14 filters+pass defaults
2026-03-23 fix startup ch13+14 dmamem error
2026-03-23 fix long press ch11
2026-03-23 fix instruments ADSR
2026-03-23 fixed CRF settings for ch11
2026-03-23 fixed midi input ch13+14
2026-03-24 freed more ram1 via pagetmp array
2026-03-24 cleaned up vars
2026-03-24 checkpoint further cleanups
2026-03-24 fixed pitch for c13+14
2026-03-24 samplesize colors
2026-03-24 added gain headroom: max 6 voices in parallel, adjustable)
2026-03-26 better loading and saving speed and progress
2026-03-27 screensaver and HFC
2026-03-27 global Mutes revisited
2026-04-08 pre-plan:sync issues
2026-04-25 finalizing firmware
2026-05-06 changed name
2026-05-06 small fixes in code, additional TPS22918DBVR for PCB (leds)
2026-05-09 fixed audio/pack loading and handling, also added eyes screensaver
2026-05-09 fixed defaults for eeprom
2026-05-11 fixed PCB: right resistors for TS + componentsize
2026-05-11 fixed PCB: right resistors for TS + componentsize - final
2026-05-18 included childMode for easy play:thank you miniBooth
2026-05-21 fixed battery display and final bugfixes for 2.2
